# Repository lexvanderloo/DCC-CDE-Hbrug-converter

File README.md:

# CDE-Hbrug-converter-DCC-
Stuurt een DCC-gebaseerd CDE-signaal naar een Hbrug. Vormt daarmee een goedkope Booster voor DCC

LET OP: NOG NIET GETEST
V11 is zojuist terug van de printfabriek en wordt binnenkort getest.

De bestanden zijn voor Kicad v5

Aan de CDE-kant wort het CDE-signaal van een centrale aangesloten
Daarnaast een DC-voeding van maximaal 18V
Aan de Hbrug-kant worden de +5V en GND op de Hbrug aangesloten. 
Daarnaast de RPW en de LPW. De beide Kortsluitmeldingen IS-left en IS-right van de Hbrug worden beide op IS aangesloten.
De CDE-signalen zijn galvanisch geschieden van de Hbrug.
U4 zorgt voor een constante spanning van 5V voor de elektronica.
De vermogensstroom voor de Hbrug komt van een aparte bron.

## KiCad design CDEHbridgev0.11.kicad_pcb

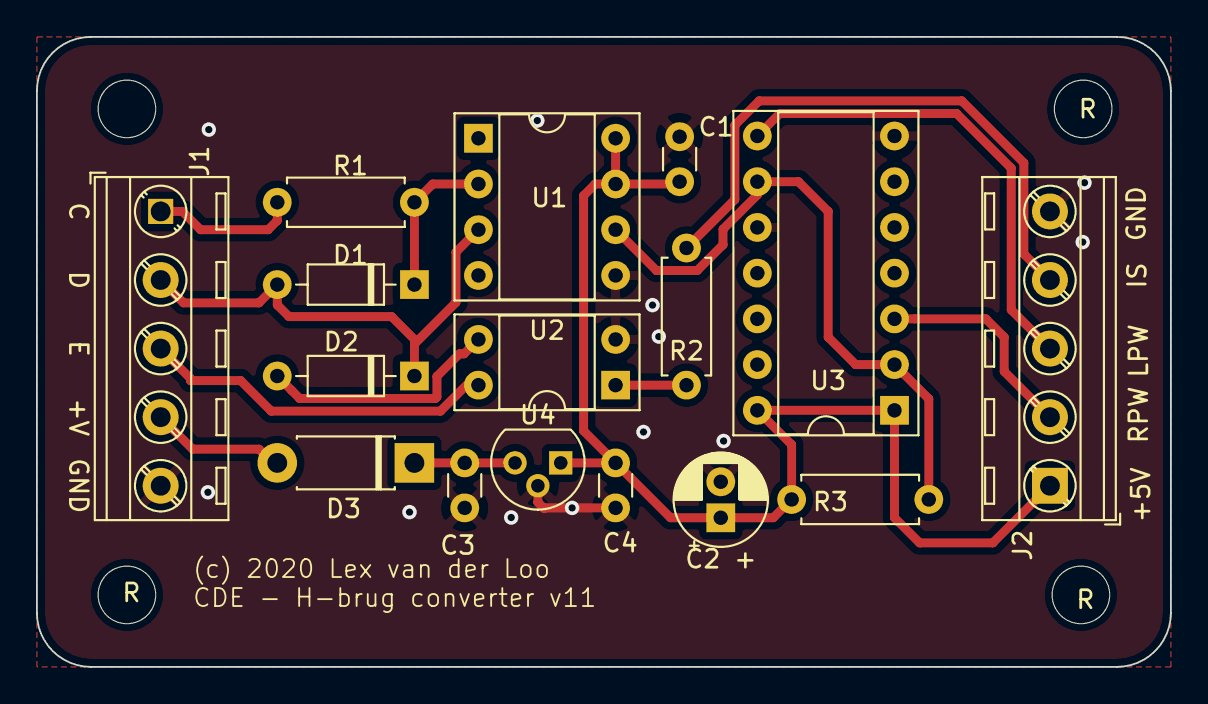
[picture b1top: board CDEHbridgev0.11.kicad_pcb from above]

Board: 2 copper layers, 63.0 x 35.0 mm, 20 parts (0 on the bottom side), 14 nets.

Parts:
C1, C3, C4: 100n; C_Disc_D3.0mm_W1.6mm_P2.50mm
C2 +: 10u; CP_Radial_D5.0mm_P2.00mm
D1, D2: 4148; D_DO-35_SOD27_P7.62mm_Horizontal
D3: 4004; D_DO-41_SOD81_P7.62mm_Horizontal
J1, J2: S; TerminalBlock_MetzConnect_Type086_RT03405HBLC_1x05_P3.81mm_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
R: 3.2mm; MountingHole_3.2mm_M3_DIN965
R1: 2k2; R_Axial_DIN0207_L6.3mm_D2.5mm_P7.62mm_Horizontal
R2, R3: 1k; R_Axial_DIN0207_L6.3mm_D2.5mm_P7.62mm_Horizontal
R#2, R#3, R#4: 3.2mm; MountingHole_3.2mm_M3_DIN965
U1: 6N137; DIP-8_W7.62mm_Socket
U2: TLP785; DIP-4_W7.62mm_Socket
U3: 74LS86; DIP-14_W7.62mm_Socket
U4: LM78L05; TO-92

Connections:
+5V: C1.1, C2 +.1, C4.1, J2.1, R3.1, U1.7, U1.8, U3.1, U3.14, U4.1
/+Voeding: D3.2, J1.4
/C: J1.1, R1.2
/D: D1.2, D2.1, J1.2, U1.3
/E: J1.3, U2.4
/LPWM: J2.3, U3.8
/RPWM: J2.2, U3.3
/R_ISenL_IS: J2.4, R2.1
GND: C1.2, C2 +.2, C3.2, C4.2, J1.5, J2.5, U1.5, U2.2, U3.7, U3.10, U4.2
unnamed: C3.1, D3.1, U4.3
unnamed: D1.1, R1.1, U1.2
unnamed: D2.2, U2.3
unnamed: R2.2, U2.1
unnamed: R3.2, U1.6, U3.2, U3.9

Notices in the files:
CDEHbridgev0.11.kicad_pcb:
(c) 2020 Lex van der Loo
